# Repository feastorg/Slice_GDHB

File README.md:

# Gate-Driven H-Bridge Slice

Gate-driven Discrete H-Bridge Slice for BREAD.

## Introduction

[Short introduction on the project.]

## Usage

[Explain how to use the project. Include examples and screenshots if applicable.]

## Documentation

Please refer to the [docs](/docs) for more info.

---

<div align="center">
  
</div>

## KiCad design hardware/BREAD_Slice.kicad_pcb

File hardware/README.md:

# Hardware Notes

- Driver A4957SESTR-T
  - https://www.digikey.ca/en/products/detail/allegro-microsystems/A4957SESTR-T/3770630
- wago terminal block:
  - https://www.digikey.ca/en/products/detail/wago-corporation/2606-1104-010-000/15538173
- MOSFETS
  - https://www.digikey.ca/en/products/detail/nexperia-usa-inc/PSMN1R0-30YLC-115/2674282
-

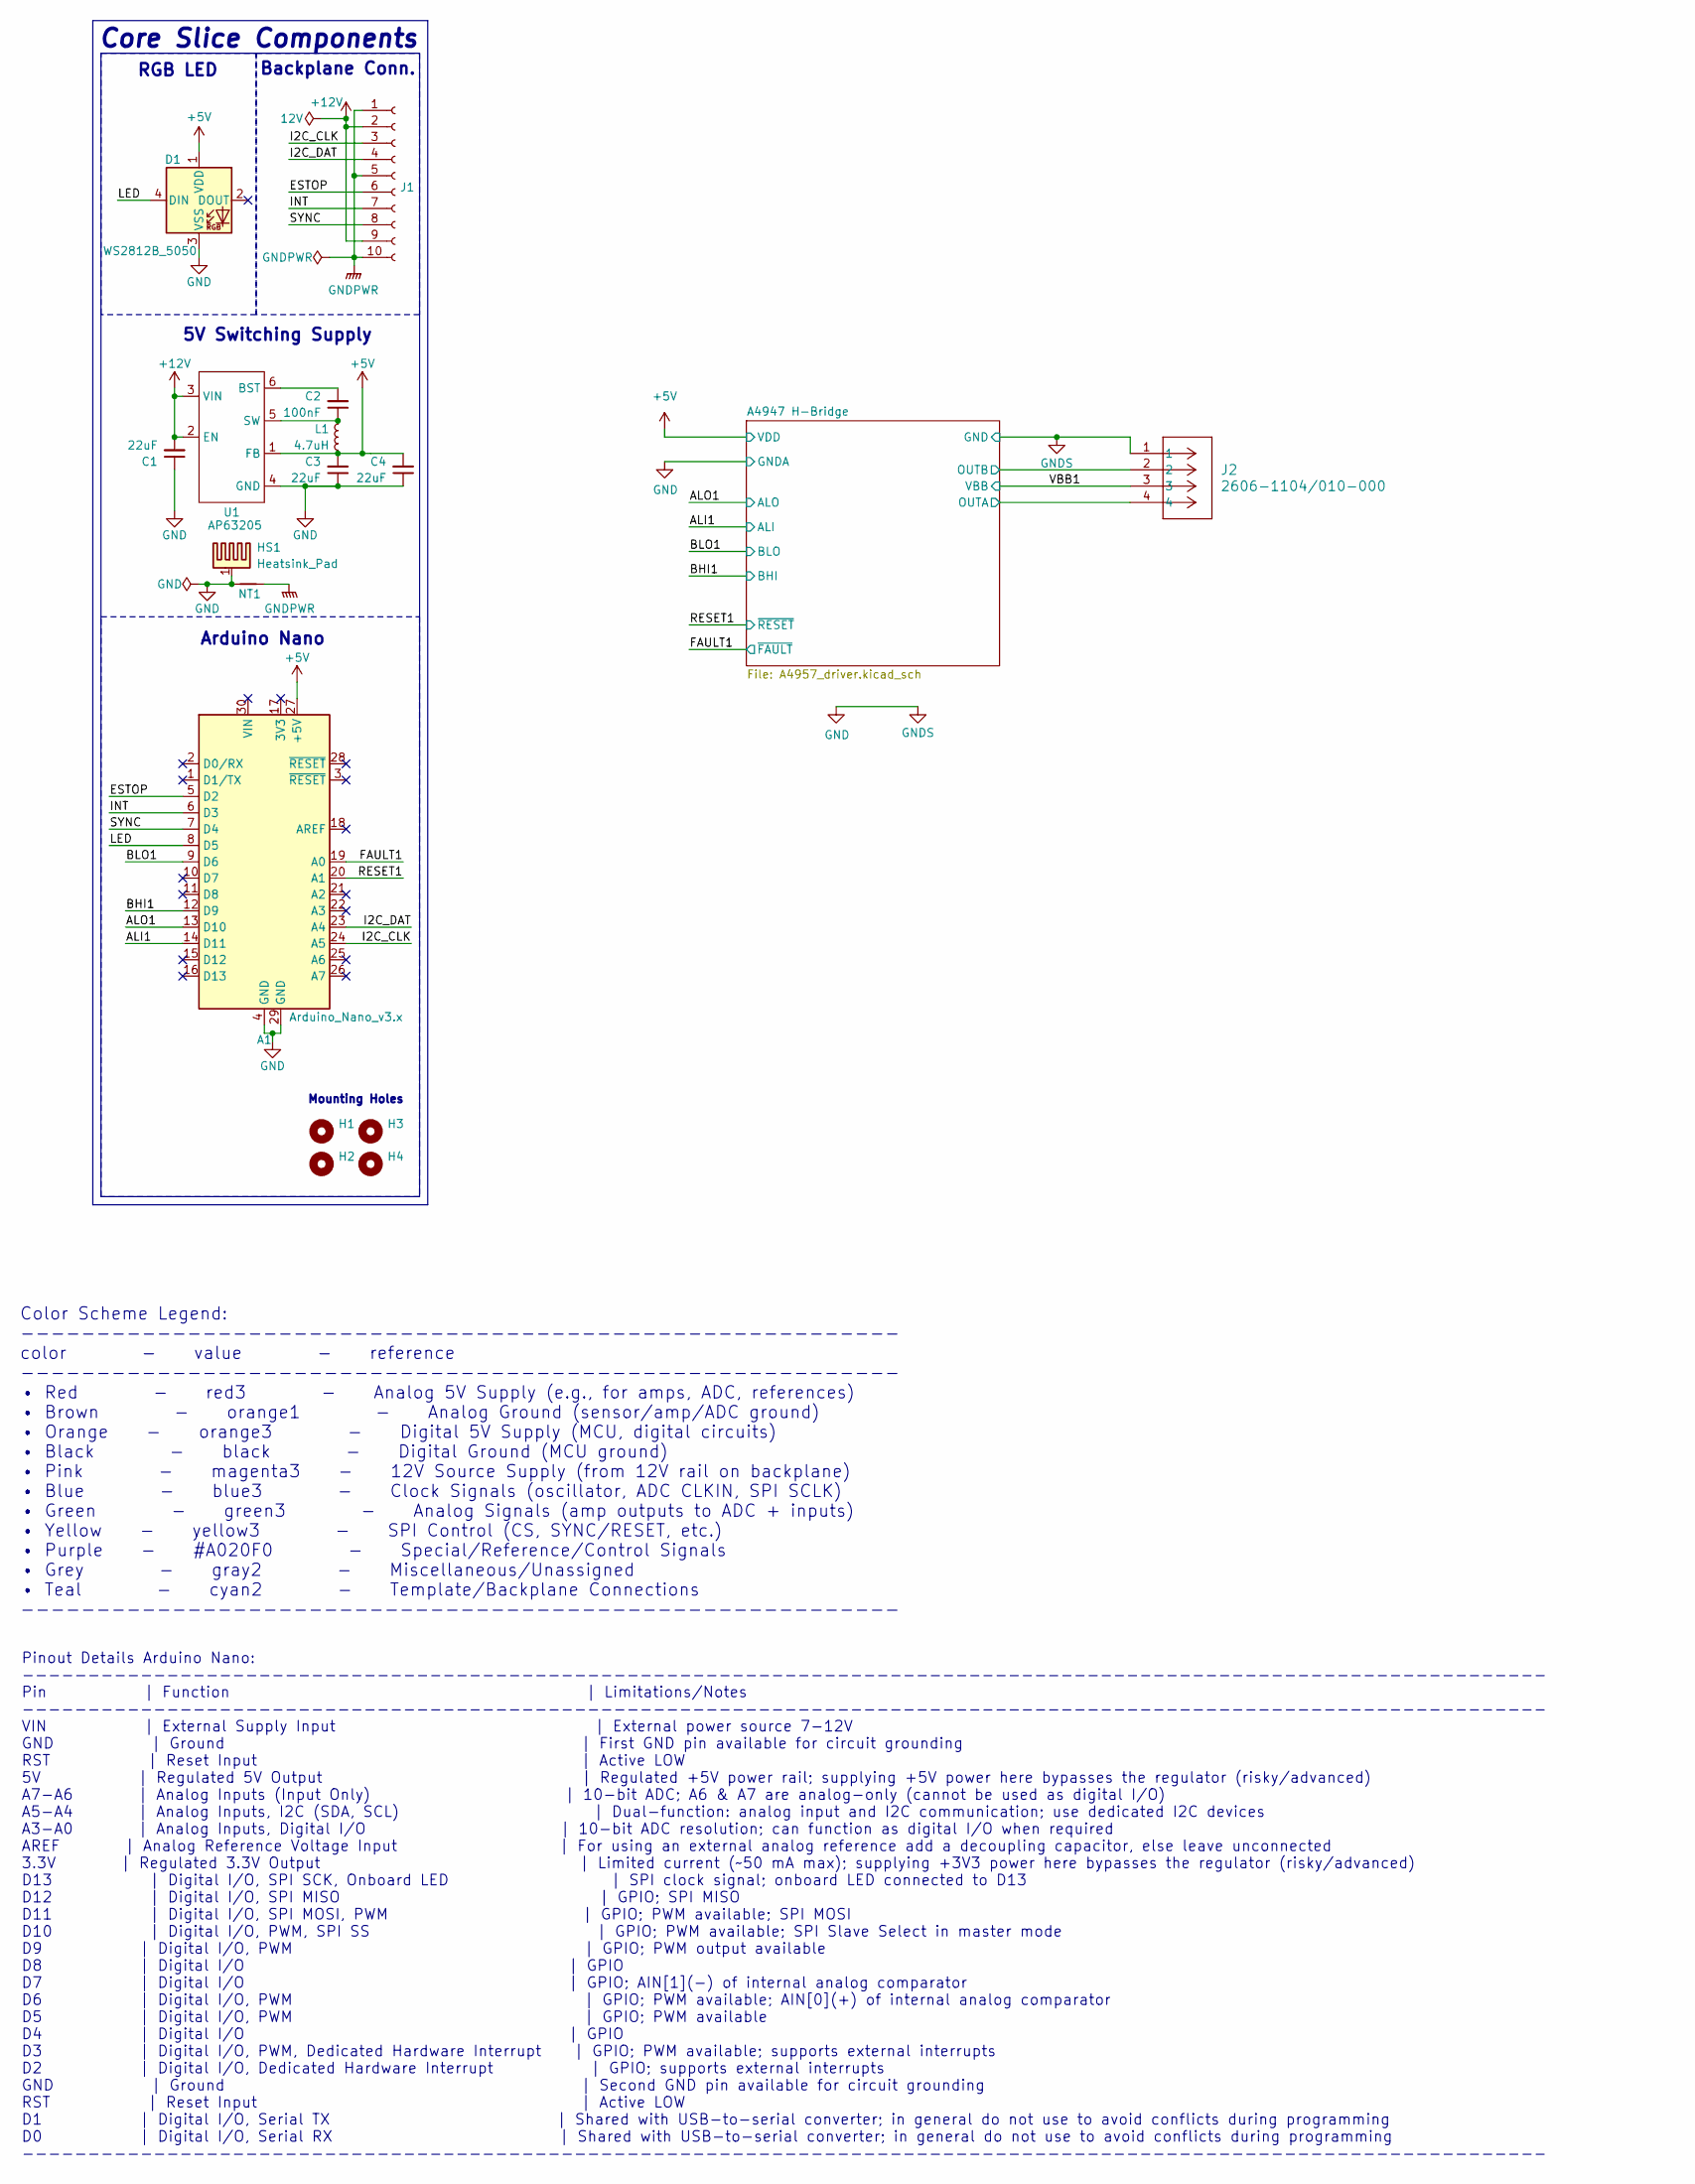
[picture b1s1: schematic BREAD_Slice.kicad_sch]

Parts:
A1: Arduino_Nano_v3.x; Arduino_Nano
C1, C3, C4: 22uF; C_1206_3216Metric_Pad1.33x1.80mm_HandSolder
C2: 100nF; C_1206_3216Metric_Pad1.33x1.80mm_HandSolder
D1: WS2812B_5050; WS2812-5050-4PIN
H1, H2, H3, H4: MountingHole; MountingHole_5mm
HS1: Heatsink_Pad; Thermal_Pad
J1: Conn_01x10_Female; PinSocket_1x10_P2.54mm_Horizontal
J2: 2606-1104/010-000; CONN4_2606-1104&slash_010-000_WAG
L1: 4.7uH; L_1210_3225Metric
NT1: NetTie_2; NetTie-2_SMD_Pad2.0mm
U1: AP63205; TSOT-23-6

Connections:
+5V: A1.27 (+5V), C3.2, C4.2, D1.1 (VDD), L1.2, U1.1 (FB); also elsewhere on the board
+12V: C1.2, J1.2, J1.9, U1.2 (EN), U1.3 (VIN)
/A4947 H-Bridge/SA: J2.4; also elsewhere on the board
/A4947 H-Bridge/SB: J2.2; also elsewhere on the board
/ALI1: A1.14 (D11); also elsewhere on the board
/ALO1: A1.13 (D10); also elsewhere on the board
/BHI1: A1.12 (D9); also elsewhere on the board
/BLO1: A1.9 (D6); also elsewhere on the board
/ESTOP: A1.5 (D2), J1.6
/FAULT1: A1.19 (A0); also elsewhere on the board
/I2C_CLK: A1.24 (A5), J1.3
/I2C_DAT: A1.23 (A4), J1.4
/INT: A1.6 (D3), J1.7
/LED: A1.8 (D5), D1.4 (DIN)
/RESET1: A1.20 (A1); also elsewhere on the board
/SYNC: A1.7 (D4), J1.8
/VBB1: J2.3; also elsewhere on the board
GND: A1.4 (GND), A1.29 (GND), C1.1, C3.1, C4.1, D1.3 (VSS), HS1.1, J2.1, NT1.1, U1.4 (GND); also elsewhere on the board
GNDPWR: J1.1, J1.5, J1.10, NT1.2
unnamed: C2.2, U1.6 (BST)
unnamed: C2.1, L1.1, U1.5 (SW)

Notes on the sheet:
5V Switching Supply
Pinout Details Arduino Nano: -------------------------------------------------------------------------------------------------------------------- Pin | Function | Limitations/Notes -------------------------------------------------------------------------------------------------------------------- V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
RGB LED
Color Scheme Legend: ---------------------------------------------------------- color - value - reference ---------------------------------------------------------- • Red - red3 - Analog 5V Supply (e.g., for amps, ADC, references) • Brown - orange1 - Analog Ground (sensor/amp/ADC ground) • Orange -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
Core Slice Components
Arduino Nano
Mounting Holes
Backplane Conn.

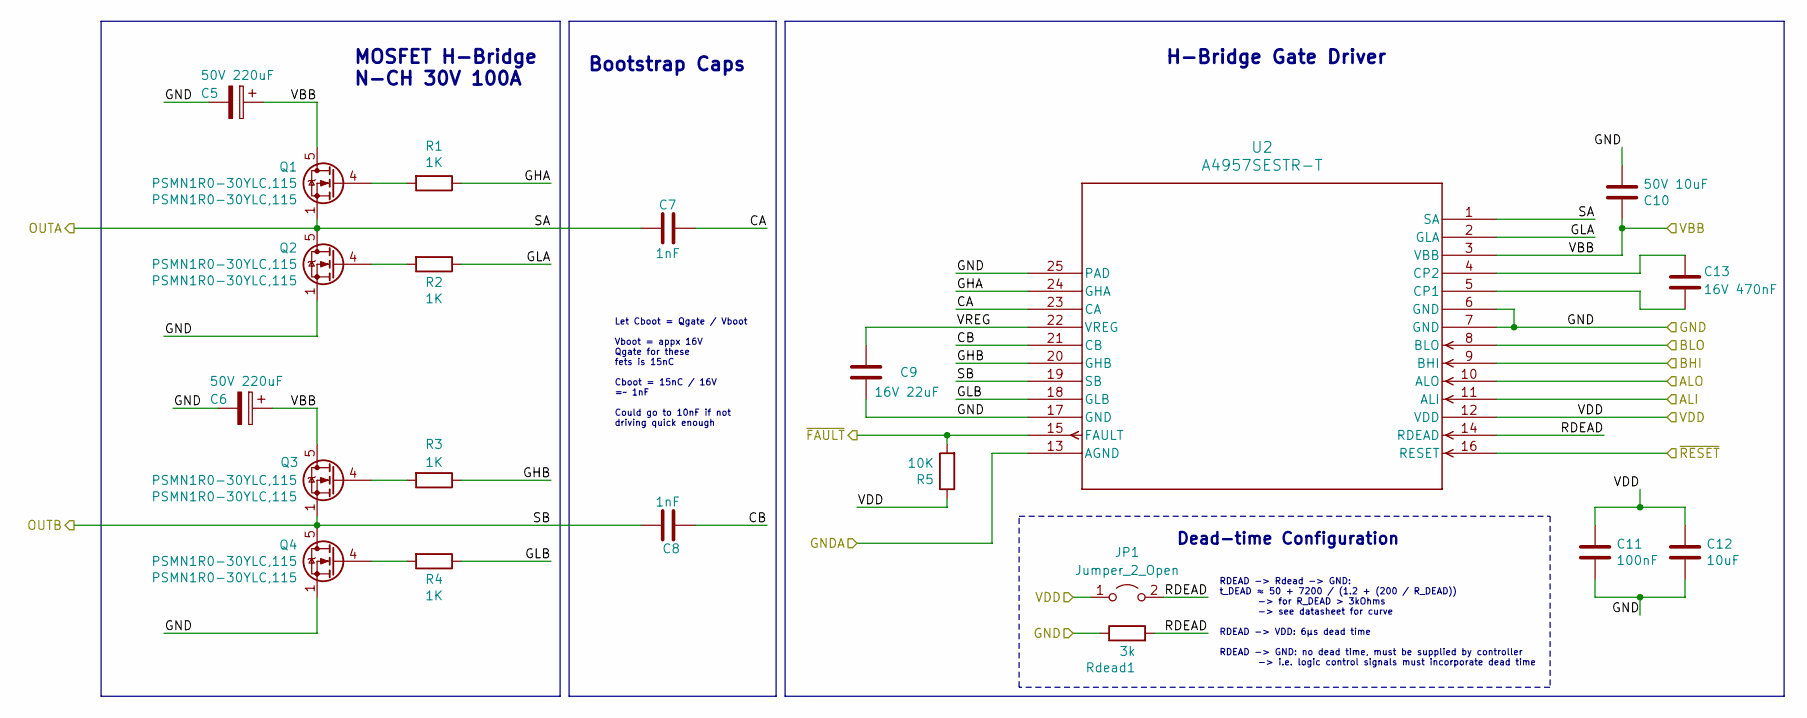
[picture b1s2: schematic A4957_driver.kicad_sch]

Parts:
C5, C6: 50V 220uF; CP_Elec_10x10
C7, C8: 1nF; C_0805_2012Metric_Pad1.18x1.45mm_HandSolder
C9: 16V 22uF; C_0805_2012Metric_Pad1.18x1.45mm_HandSolder
C10: 50V 10uF; C_0805_2012Metric_Pad1.18x1.45mm_HandSolder
C11: 100nF; C_0805_2012Metric_Pad1.18x1.45mm_HandSolder
C12: 10uF; C_0805_2012Metric_Pad1.18x1.45mm_HandSolder
C13: 16V 470nF; C_0805_2012Metric_Pad1.18x1.45mm_HandSolder
JP1: Jumper_2_Open; C_0805_2012Metric
Q1, Q2, Q3, Q4: PSMN1R0-30YLC,115; LFPAK56; MPN PSMN1R0-30YLC,115
R1, R2, R3, R4: 1K; R_0805_2012Metric_Pad1.20x1.40mm_HandSolder
R5: 10K; R_0805_2012Metric_Pad1.20x1.40mm_HandSolder
Rdead1: 3k; R_0805_2012Metric_Pad1.20x1.40mm_HandSolder
U2: A4957SESTR-T; QFN-24_ALM

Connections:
+5V: C11.1, C12.1, JP1.1 (A), R5.1, U2.12 (VDD); also elsewhere on the board
/A4947 H-Bridge/CA: C7.2, U2.23 (CA)
/A4947 H-Bridge/CB: C8.2, U2.21 (CB)
/A4947 H-Bridge/GHA: R1.1, U2.24 (GHA)
/A4947 H-Bridge/GHB: R3.1, U2.20 (GHB)
/A4947 H-Bridge/GLA: R2.1, U2.2 (GLA)
/A4947 H-Bridge/GLB: R4.1, U2.18 (GLB)
/A4947 H-Bridge/RDEAD: JP1.2 (B), Rdead1.2, U2.14 (RDEAD)
/A4947 H-Bridge/SA: C7.1, Q1.1 (S), Q1.2 (S), Q1.3 (S), Q2.5 (D), U2.1 (SA); also elsewhere on the board
/A4947 H-Bridge/SB: C8.1, Q3.1 (S), Q3.2 (S), Q3.3 (S), Q4.5 (D), U2.19 (SB); also elsewhere on the board
/A4947 H-Bridge/VREG: C9.1, U2.22 (VREG)
/ALI1: U2.11 (ALI); also elsewhere on the board
/ALO1: U2.10 (ALO); also elsewhere on the board
/BHI1: U2.9 (BHI); also elsewhere on the board
/BLO1: U2.8 (BLO); also elsewhere on the board
/FAULT1: R5.2, U2.15 (FAULT); also elsewhere on the board
/RESET1: U2.16 (RESET); also elsewhere on the board
/VBB1: C5.1, C6.1, C10.1, Q1.5 (D), Q3.5 (D), U2.3 (VBB); also elsewhere on the board
GND: C5.2, C6.2, C9.2, C10.2, C11.2, C12.2, Q2.1 (S), Q2.2 (S), Q2.3 (S), Q4.1 (S), Q4.2 (S), Q4.3 (S), Rdead1.1, U2.6 (GND), U2.7 (GND), U2.13 (AGND), U2.17 (GND), U2.25 (PAD); also elsewhere on the board
unnamed: Q1.4 (G), R1.2
unnamed: Q2.4 (G), R2.2
unnamed: Q3.4 (G), R3.2
unnamed: Q4.4 (G), R4.2
unnamed: C13.1, U2.5 (CP1)
unnamed: C13.2, U2.4 (CP2)

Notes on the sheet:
Dead-time Configuration
Let Cboot = Qgate / Vboot Vboot = appx 16V Qgate for these fets is 15nC Cboot = 15nC / 16V =~ 1nF Could go to 10nF if not driving quick enough
Bootstrap Caps
RDEAD -> Rdead -> GND: t_DEAD ≈ 50 + 7200 / (1.2 + (200 / R_DEAD)) -> for R_DEAD > 3kOhms -> see datasheet for curve RDEAD -> VDD: 6µs dead time RDEAD -> GND: no dead time, must be supplied by controller -> i.e. logic control signals must incorporate dead time
H-Bridge Gate Driver
MOSFET H-Bridge N-CH 30V 100A

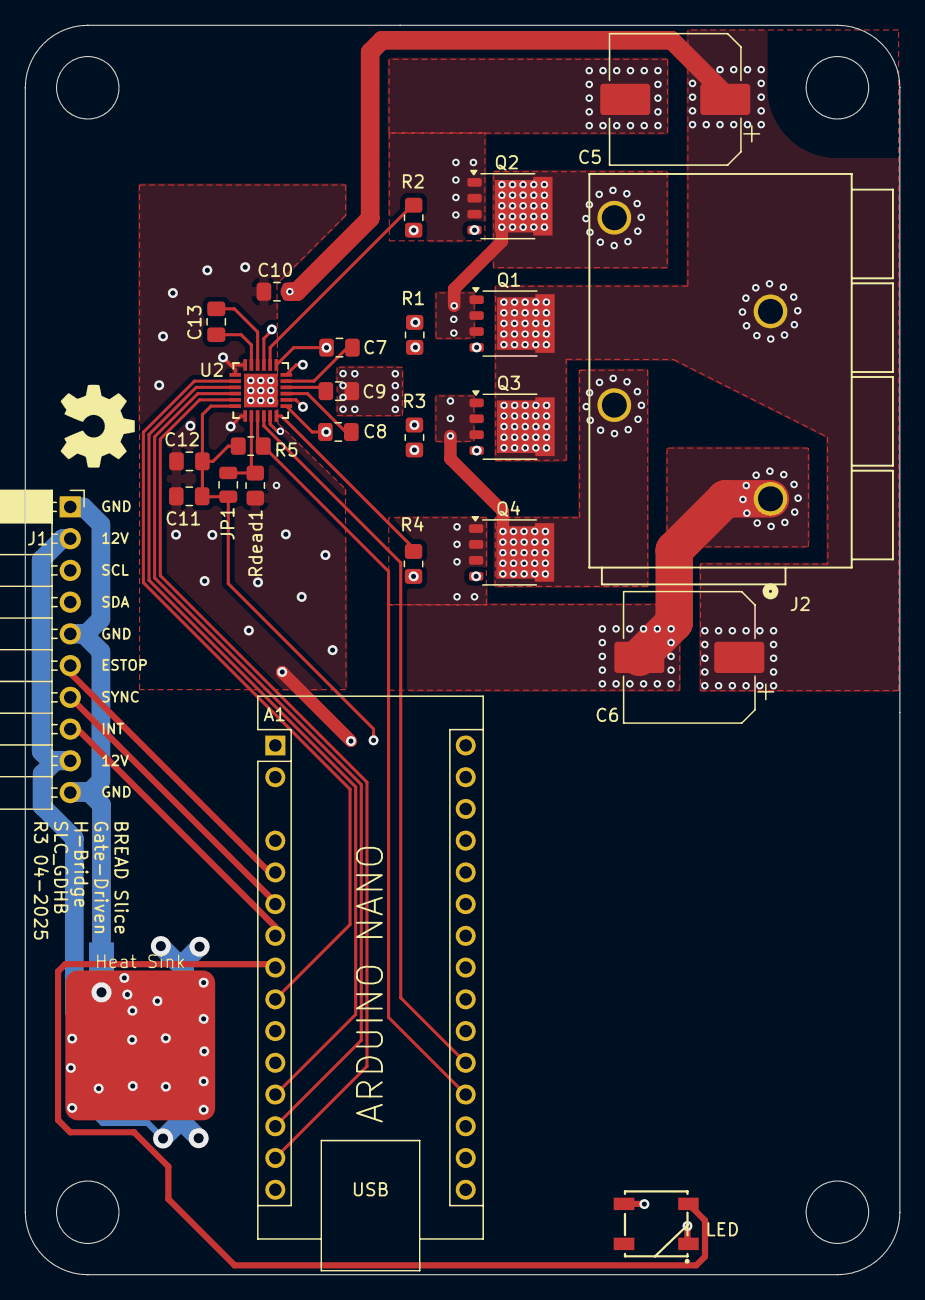
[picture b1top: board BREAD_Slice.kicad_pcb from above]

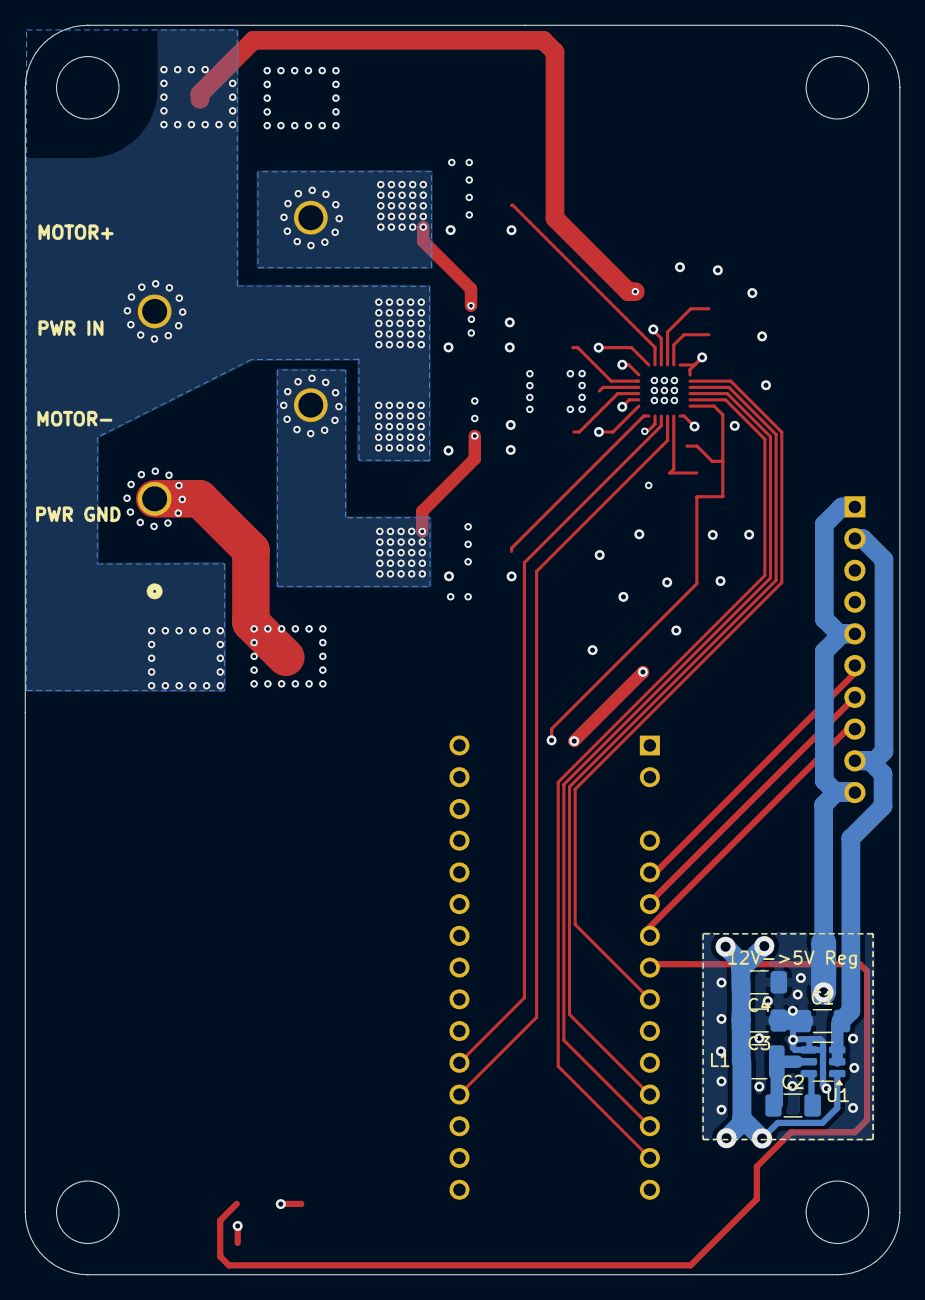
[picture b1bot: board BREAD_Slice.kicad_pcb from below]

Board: 4 copper layers, 70.0 x 100.0 mm, 38 parts (7 on the bottom side), 35 nets.

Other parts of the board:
Logo1: Logo_Open_Hardware_Small; OSHW-Symbol_6.7x6mm_SilkScreen

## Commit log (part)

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2024-07-10 initial layout poisitions done
2024-09-10 set repo
2025-04-10 finished initial schematic and board
2025-04-10 removed old
2025-04-10 added hw readme
2025-04-10 updated hw readme
2026-04-18 chore: generate gerbers
2026-05-20 Add slice.yaml manifest (schema v1.0)
2026-05-24 Add KiBot/docs pipeline (4-layer)
2026-05-24 Update TODO with CI findings (DRC+ERC errors)
